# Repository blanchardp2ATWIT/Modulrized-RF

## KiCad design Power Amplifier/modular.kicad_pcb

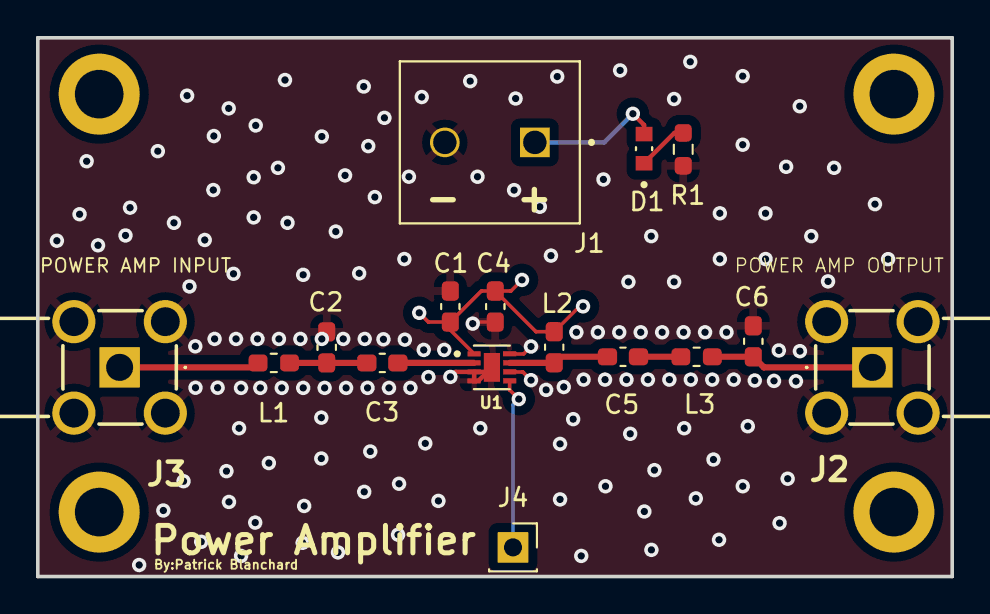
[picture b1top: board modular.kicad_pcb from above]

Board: 4 copper layers, 50.8 x 29.9 mm, 16 parts (0 on the bottom side), 10 nets.

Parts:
C1, C4: 1 uF; C_0603_1608Metric_Pad1.08x0.95mm_HandSolder
C2: 860 fF; C_0603_1608Metric_Pad1.08x0.95mm_HandSolder
C3, C5: 1 nF; C_0603_1608Metric_Pad1.08x0.95mm_HandSolder
C6: 4.635 pF; C_0603_1608Metric_Pad1.08x0.95mm_HandSolder
D1: -; LEDC1608X35N
J1: -; PHOENIX_1935776
J2, J3: 50 ohm; 518144002
J4: Conn_01x01_Pin; PinSocket_1x01_P2.54mm_Vertical
L1: 7.34 nH; L_0603_1608Metric_Pad1.05x0.95mm_HandSolder
L2: 100 nH; C_0603_1608Metric_Pad1.08x0.95mm_HandSolder
L3: 11.515 nH; L_0603_1608Metric_Pad1.05x0.95mm_HandSolder
R1: 1k; R_0603_1608Metric_Pad0.98x0.95mm_HandSolder
U1: -; SON50P200X200X80-9N

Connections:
+3.3V: C1.2, C4.2, D1.A, J1.01, L2.1, U1.1 (VCC)
GND: C1.1, C2.2, C4.1, C6.2, J1.02, J2.2, J2.3, J2.4, J2.5, J3.2, J3.3, J3.4, J3.5, R1.1, U1.3 (GND), U1.4 (GND), U1.6 (GND), U1.8 (GND), U1.9
unnamed: C2.1, C3.1, L1.2
unnamed: C5.2, L3.1
unnamed: D1.C, R1.2
unnamed: J4.1, U1.5 (!EN)
unnamed: C3.2, U1.2 (IN)
unnamed: C5.1, L2.2, U1.7 (OUT)
Power_Amp_In: J3.1, L1.1
Power_Amp_Out: C6.1, J2.1, L3.2

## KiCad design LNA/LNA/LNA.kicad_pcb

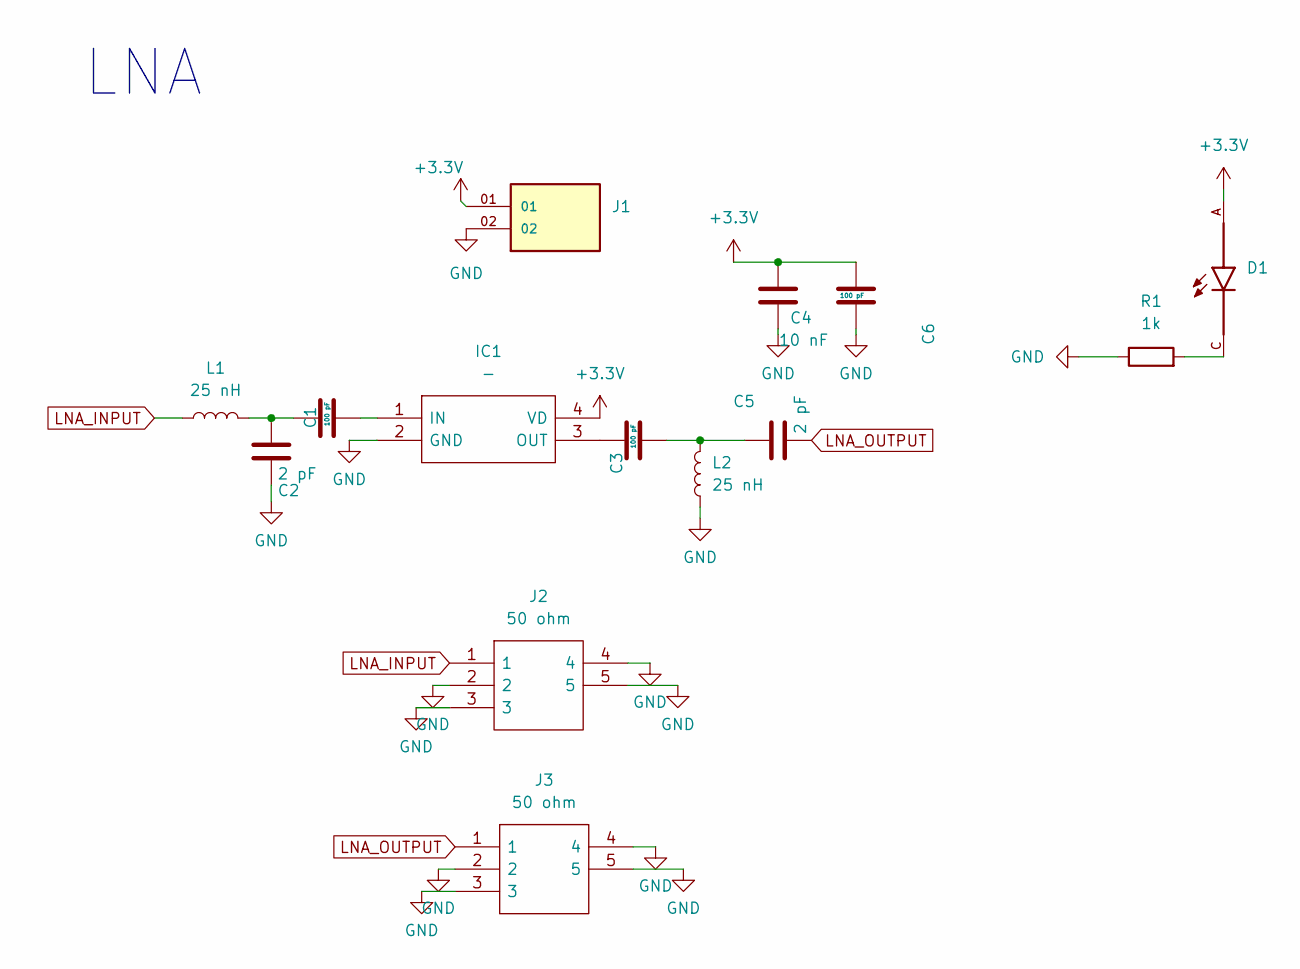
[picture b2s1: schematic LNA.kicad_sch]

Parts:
C1, C5: 2 pF; C_0603_1608Metric_Pad1.08x0.95mm_HandSolder; Part Number 885012006047
C2, C3, C6: 100 pF; C_0603_1608Metric_Pad1.08x0.95mm_HandSolder; Part Number 885012006023
C4: 10 nF; C_0603_1608Metric_Pad1.08x0.95mm_HandSolder; Part Number 885012006002
D1: -; LEDC1608X35N; Part Number LTST-C190KRKT
IC1: -; SOT343; Part Number BGA420H6327XTSA1
J1: -; PHOENIX_1935776; Part Number 1935776
J2, J3: 50 ohm; 518144002; Part Number 5-1814400-2
L1, L2: 25 nH; L_0603_1608Metric_Pad1.05x0.95mm_HandSolder; Part Number SDWL1608CP24NJSTF
R1: 1k; R_0603_1608Metric_Pad0.98x0.95mm_HandSolder; Part Number ERJ-3GEYJ102V

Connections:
+3.3V: C4.1, C6.1, D1.A, IC1.4 (VD), J1.01
GND: C1.2, C4.2, C6.2, IC1.2 (GND), J1.02, J2.2, J2.3, J2.4, J2.5, J3.2, J3.3, J3.4, J3.5, L2.1, R1.1
LNA_INPUT: J2.1, L1.1
LNA_OUTPUT: C5.2, J3.1
unnamed: C1.1, C2.2, L1.2
unnamed: C3.1, C5.1, L2.2
unnamed: D1.C, R1.2
unnamed: C2.1, IC1.1 (IN)
unnamed: C3.2, IC1.3 (OUT)

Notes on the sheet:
LNA

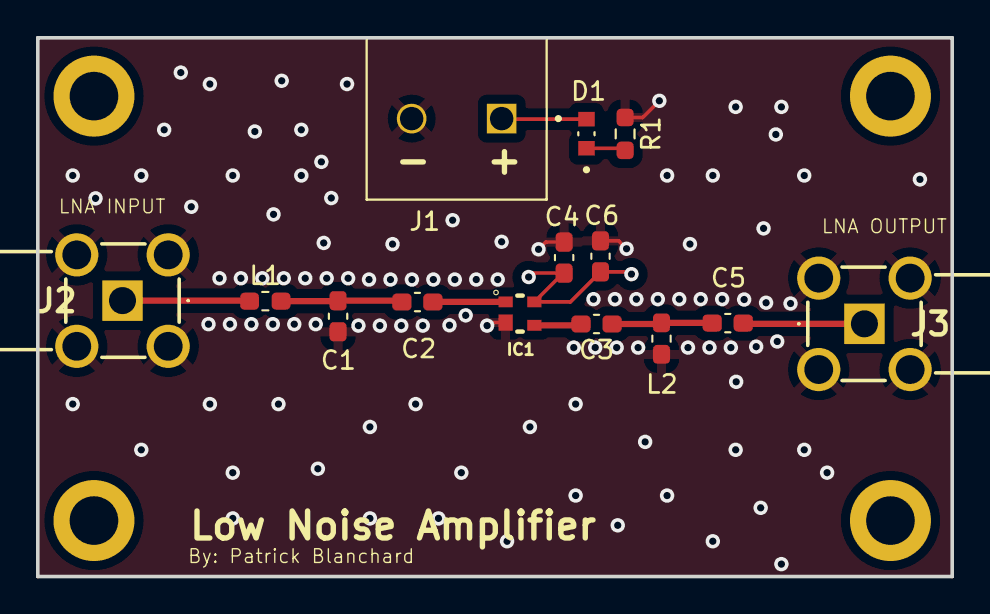
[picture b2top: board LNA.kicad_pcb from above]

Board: 4 copper layers, 50.8 x 29.9 mm, 14 parts (0 on the bottom side), 9 nets.

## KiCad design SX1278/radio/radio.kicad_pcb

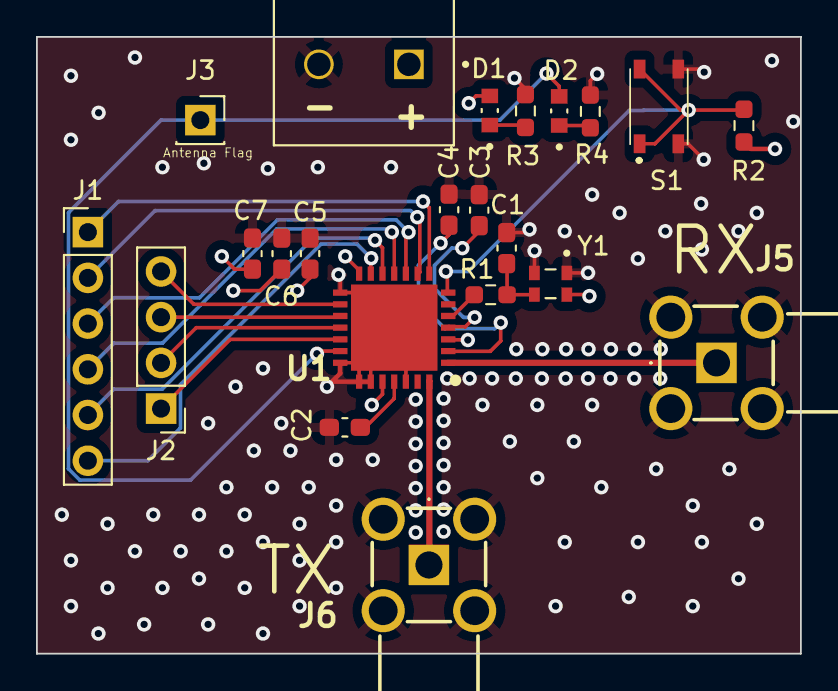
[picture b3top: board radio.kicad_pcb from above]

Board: 4 copper layers, 42.4 x 34.3 mm, 22 parts (0 on the bottom side), 23 nets.

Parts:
C1: 10 pF; C_0603_1608Metric_Pad1.08x0.95mm_HandSolder
C2, C3, C4, C6: 100 nF; C_0603_1608Metric_Pad1.08x0.95mm_HandSolder
C5: 1 uF; C_0603_1608Metric_Pad1.08x0.95mm_HandSolder
C7: 4.7 uF; C_0603_1608Metric_Pad1.08x0.95mm_HandSolder
D1, D2: -; LEDC1608X35N
J1: DO NOT PLACE; PinHeader_1x06_P2.54mm_Vertical
J2: DO NOT PLACE; PinHeader_1x04_P2.54mm_Vertical
J3: Conn_01x01_Pin; PinSocket_1x01_P2.54mm_Vertical
J4: -; PHOENIX_1935776
J5, J6: 50 ohm; 518144002
R1: 9.9k; R_0603_1608Metric_Pad0.98x0.95mm_HandSolder
R2: 4.7k; R_0603_1608Metric_Pad0.98x0.95mm_HandSolder
R3, R4: 1k; R_0603_1608Metric_Pad0.98x0.95mm_HandSolder
S1: -; PTS810SJG250SMTRLFS
U1: -; QFN65P600X600X100-29N-D
Y1: 32 MHz; XTAL_ASTX-13-D-32.000MHz-I05-T

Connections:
+3.3V: C5.1, C6.1, C7.1, D1.A, J4.01, R2.1, U1.3 (VBAT_ANA), U1.14 (VBAT_DIG), U1.24 (VBAT_RF), Y1.4 (+VCC)
/DIO0: J1.1, U1.8 (DIO0)
/DIO1: J1.2, U1.9 (DIO1/DCLK)
/DIO2: J1.3, U1.10 (DIO2/DATA)
/DIO3: J1.4, U1.11 (DIO3)
/DIO4: J1.5, U1.12 (DIO4)
/DIO5: J1.6, U1.13 (DIO5)
Antenna_State: D2.A, J3.1, U1.20 (RXTX/RFMOD)
GND: C1.2, C2.2, C3.2, C4.2, C5.2, C6.2, C7.2, J4.02, J5.2, J5.3, J5.4, J5.5, J6.2, J6.3, J6.4, J6.5, R3.1, R4.1, S1.3, S1.4, U1.15 (GND), U1.21 (GND), U1.22 (GND), U1.23 (GND), U1.26 (GND), U1.29 (EXP), Y1.1 (GND), Y1.2 (GND)
LNA_OUTPUT: J5.1, U1.1 (RFI_LF)
unnamed: D1.C, R3.2
unnamed: D2.C, R4.2
unnamed: J2.1, U1.19 (~SS)
unnamed: J2.2, U1.18 (MOSI)
unnamed: J2.3, U1.17 (MISO)
unnamed: J2.4, U1.16 (SCK)
unnamed: C4.1, U1.2 (VR_ANA)
unnamed: C3.1, U1.4 (VR_DIG)
unnamed: C2.1, U1.25 (VR_PA)
unnamed: R1.2, U1.5 (XTA)
unnamed: R2.2, S1.1, S1.2, U1.7 (~RESET)
unnamed: C1.1, R1.1, Y1.3 (OUTPUT)
Power_Amp_In: J6.1, U1.28 (RFO_LF)

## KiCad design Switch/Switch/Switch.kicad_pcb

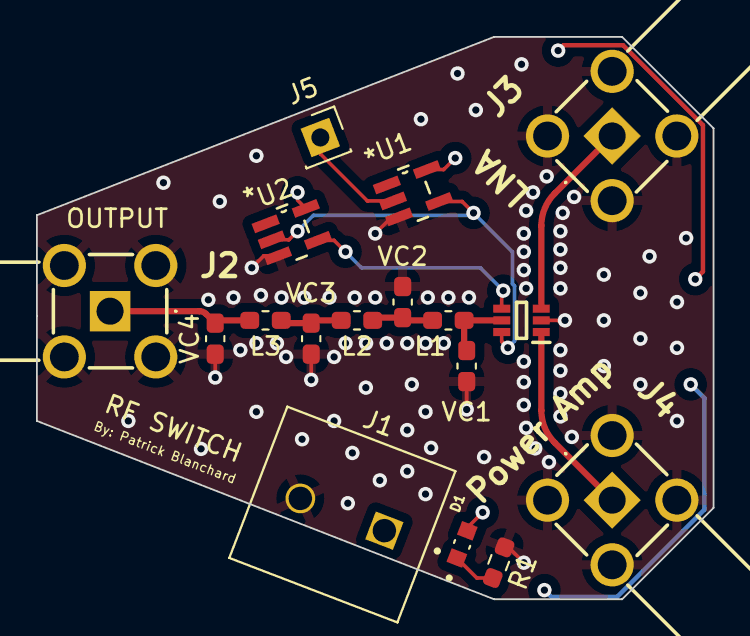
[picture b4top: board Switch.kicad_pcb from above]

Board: 4 copper layers, 37.6 x 31.2 mm, 17 parts (0 on the bottom side), 12 nets.

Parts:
D1: -; LEDC1608X35N
J1: -; PHOENIX_1935776
J2, J3, J4: 50 ohm; 518144002
J5: Conn_01x01_Pin; PinSocket_1x01_P2.54mm_Vertical
L1, L3: 20.5 nH; L_0603_1608Metric_Pad1.05x0.95mm_HandSolder
L2: 22.7 nH; L_0603_1608Metric_Pad1.05x0.95mm_HandSolder
Power Amp: -; SOT65P220X110-6N
R1: 1k; R_0603_1608Metric_Pad0.98x0.95mm_HandSolder
U1, U2: -; DBV5
VC1, VC4: 6.8 pF; C_0603_1608Metric_Pad1.08x0.95mm_HandSolder
VC2, VC3: 12.1 pF; C_0603_1608Metric_Pad1.08x0.95mm_HandSolder

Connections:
+3.3V: D1.A, J1.01, U1.5 (VCC), U2.5 (VCC)
Filter_input: L1.1, Power Amp.5 (J1), VC1.2
Filter_output: J2.1, L3.2, VC4.2
GND: J1.02, J2.2, J2.3, J2.4, J2.5, J3.2, J3.3, J3.4, J3.5, J4.2, J4.3, J4.4, J4.5, Power Amp.2 (GND), R1.1, U1.3 (GND), U2.3 (GND), VC1.1, VC2.1, VC3.1, VC4.1
LNA_INPUT: J3.1, Power Amp.3 (J2)
unnamed: D1.C, R1.2
unnamed: Power Amp.4 (V1), U2.4 (Y)
unnamed: Power Amp.6 (V2), U1.4 (Y), U2.2 (A)
unnamed: J5.1, U1.2 (A)
unnamed: L1.2, L2.1, VC2.2
unnamed: L2.2, L3.1, VC3.2
Power_Amp_Out: J4.1, Power Amp.1 (J3)

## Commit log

2024-09-08 Initial
